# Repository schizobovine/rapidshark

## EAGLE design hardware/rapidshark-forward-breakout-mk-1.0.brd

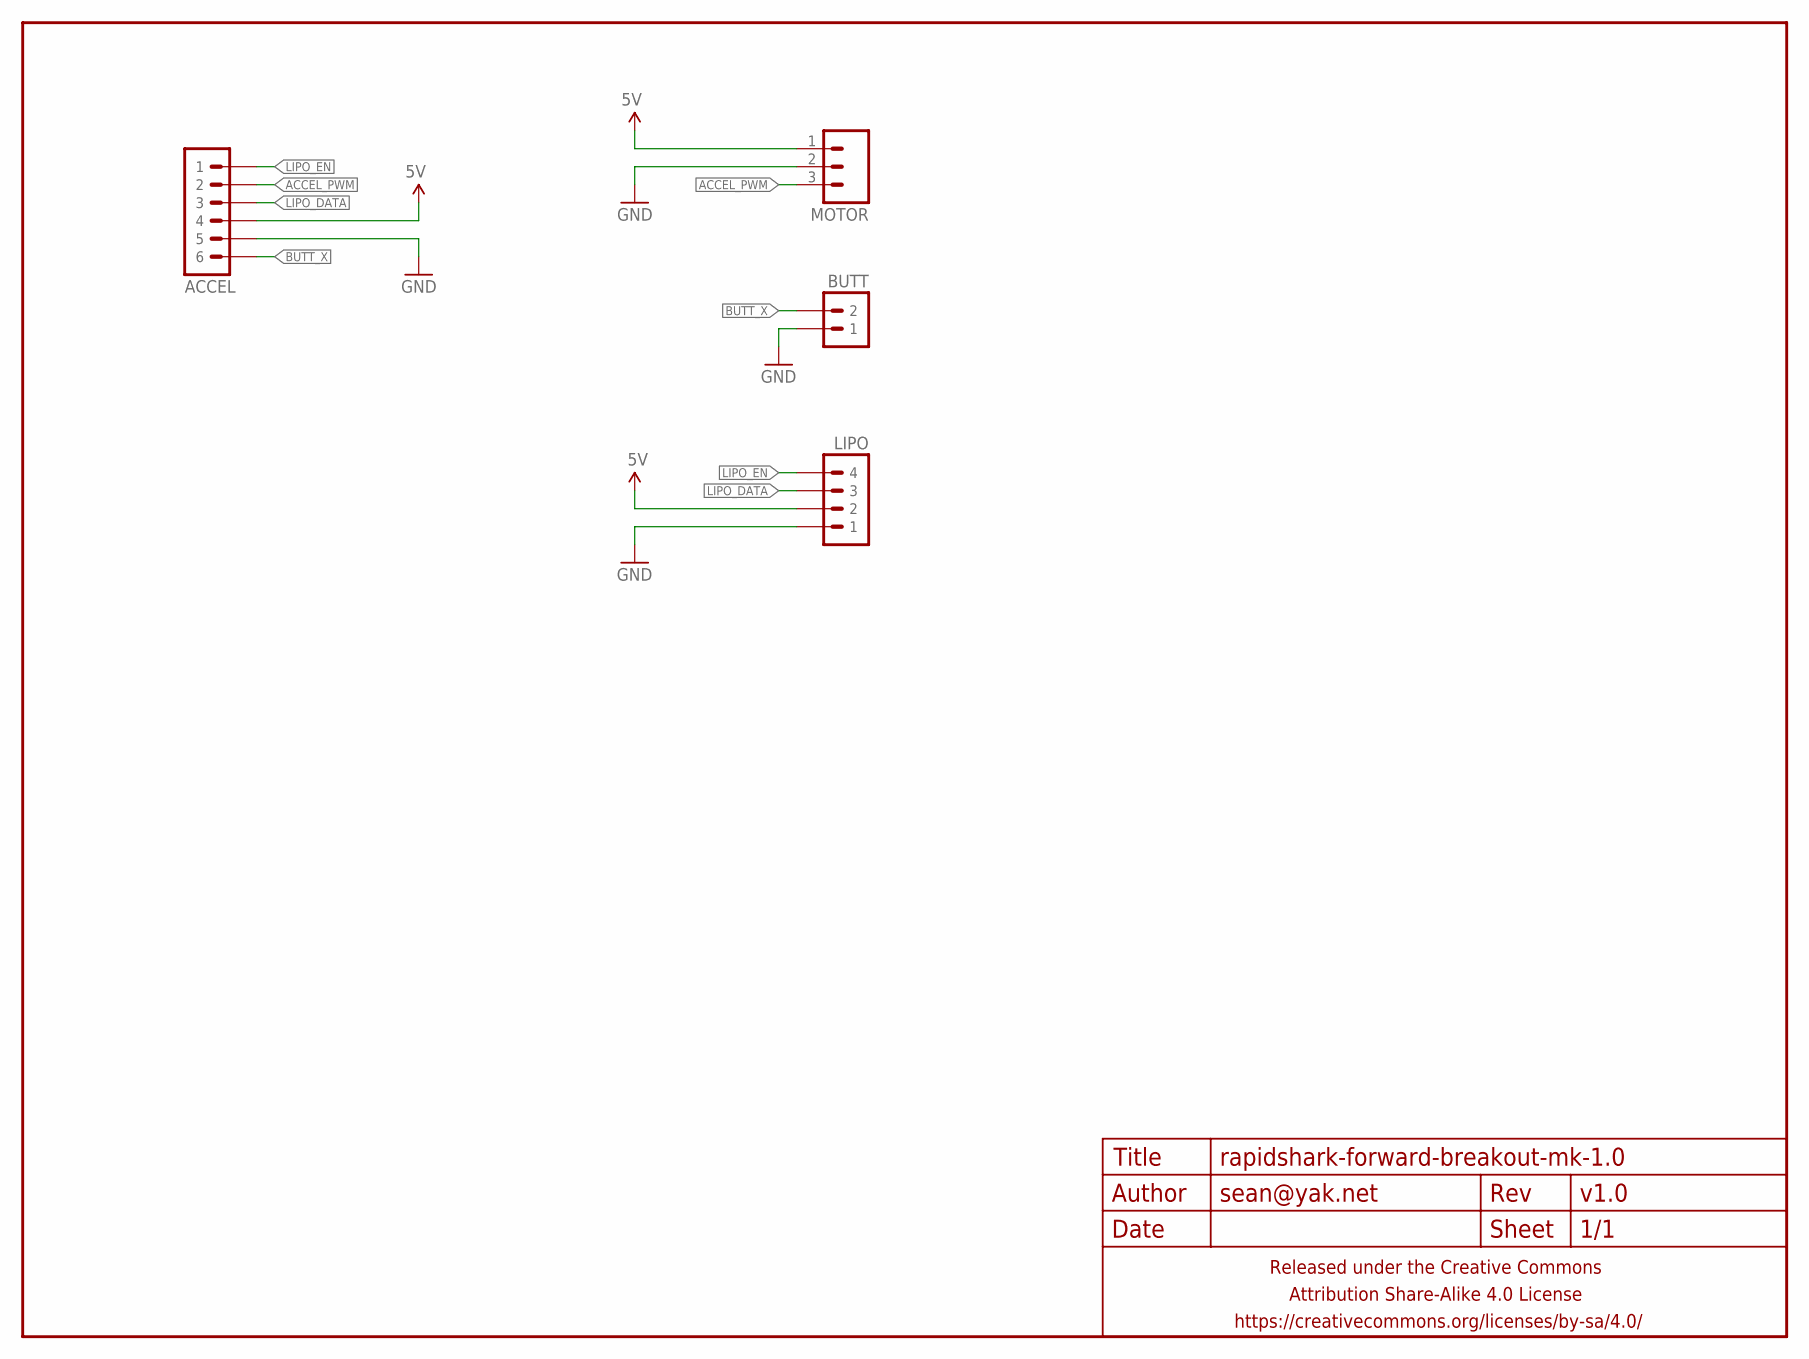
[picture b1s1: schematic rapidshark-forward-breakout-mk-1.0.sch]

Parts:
ACCEL: M06JST-PH-PTH-VERT; JST-6-PH-VERT-PTH
BUTT: M02JST-PTH-VERT; JST-2-PH-VERT-PTH
FRAME1: FRAME-LETTERNO_PACKAGE; DUMMY
LIPO: M04JST-PTH-VERT; JST-4-PH-VERT-PTH
MOTOR: M03JST-PTH-VERT; JST-3-PH-VERT-PTH

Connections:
5V: ACCEL.4, LIPO.2, MOTOR.1
ACCEL_PWM: ACCEL.2, MOTOR.3
BUTT_X: ACCEL.6, BUTT.2
GND: ACCEL.5, BUTT.1, LIPO.1, MOTOR.2
LIPO_DATA: ACCEL.3, LIPO.3
LIPO_EN: ACCEL.1, LIPO.4

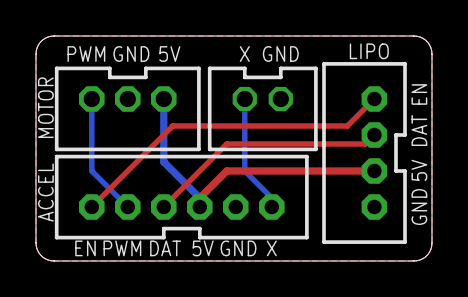
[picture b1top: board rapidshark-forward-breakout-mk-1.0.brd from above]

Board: 2 copper layers, 22.0 x 12.5 mm, 5 parts (1 on the bottom side), 6 nets.

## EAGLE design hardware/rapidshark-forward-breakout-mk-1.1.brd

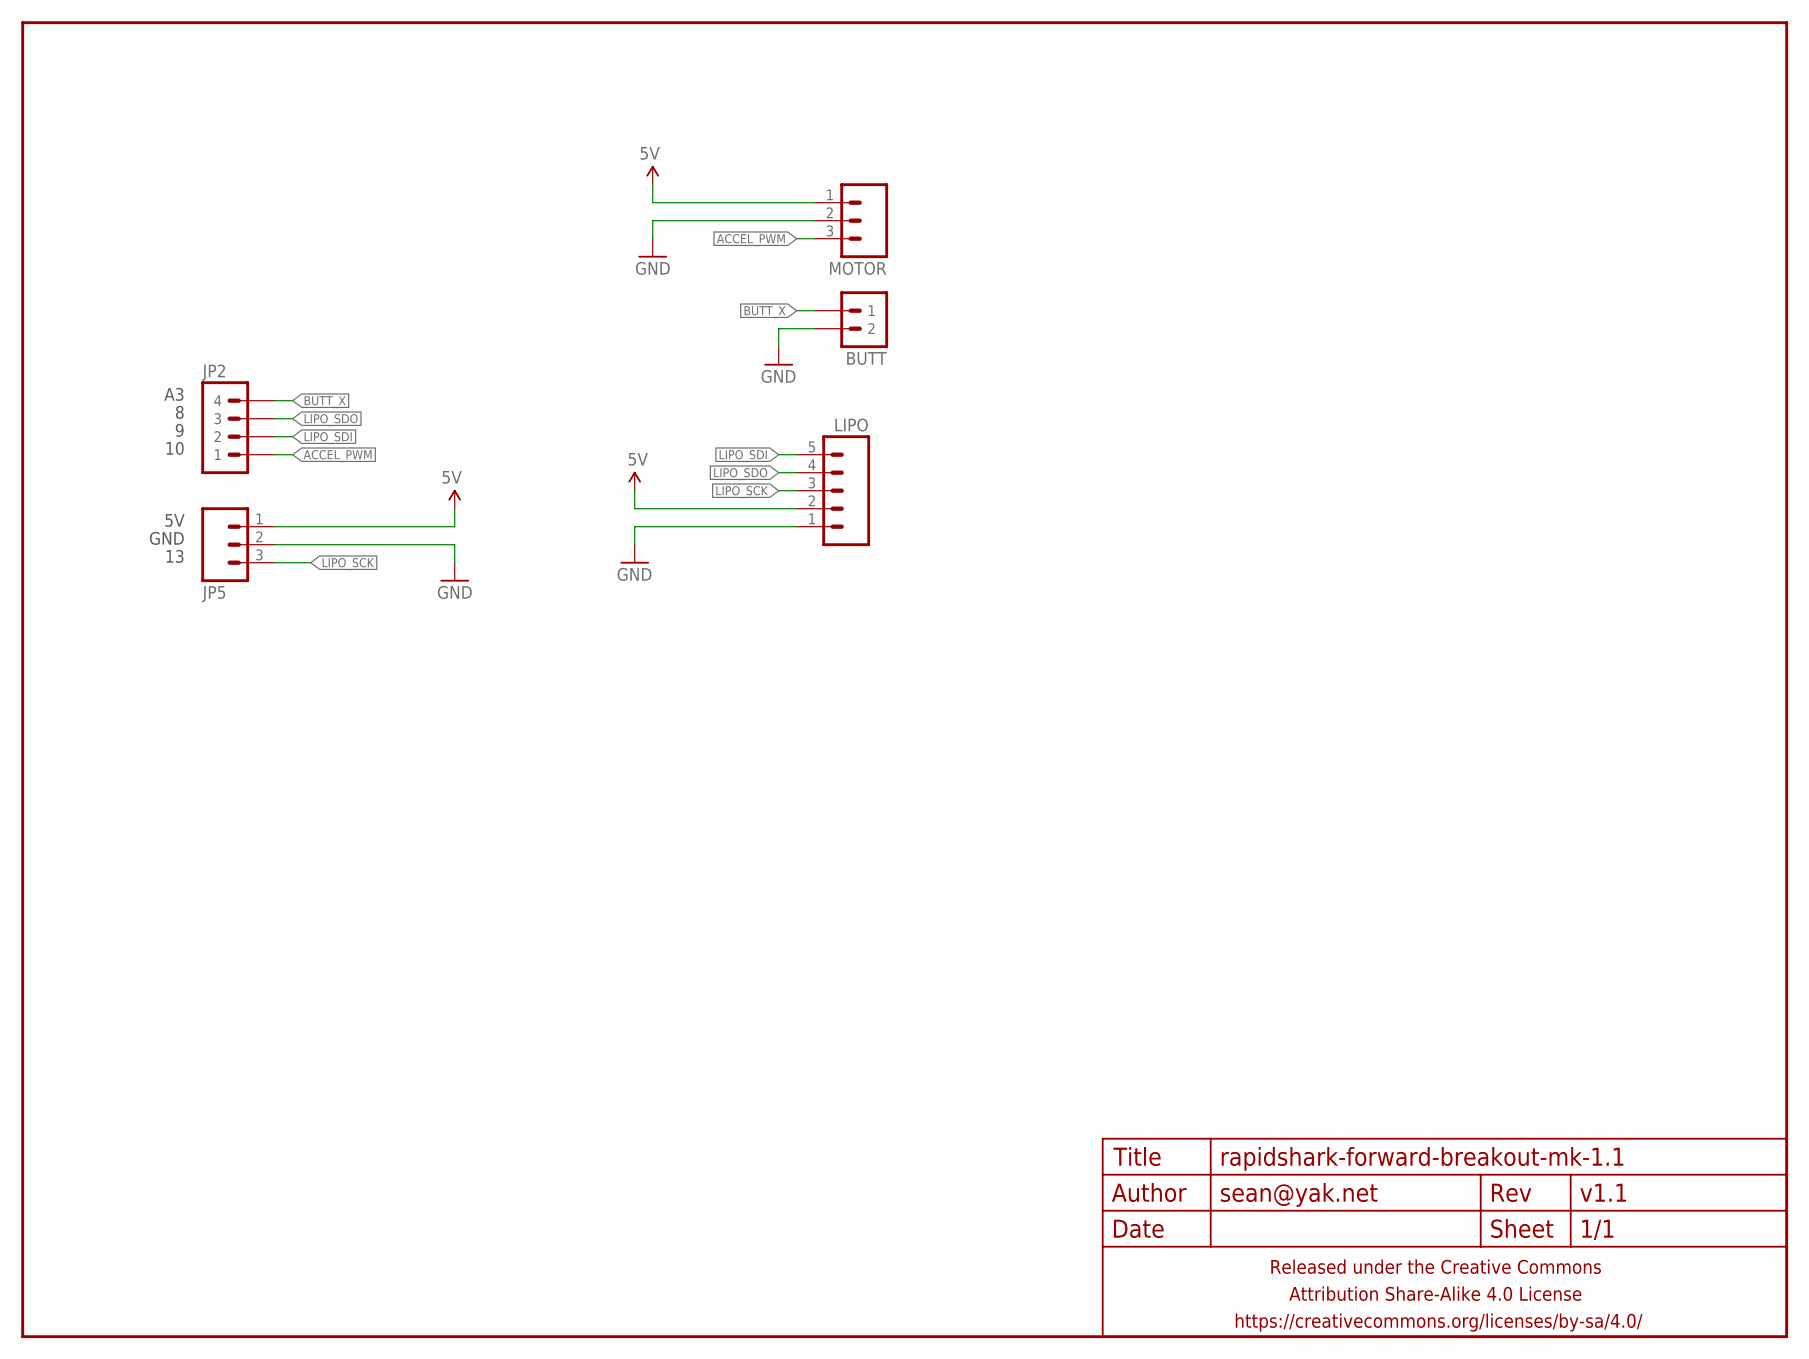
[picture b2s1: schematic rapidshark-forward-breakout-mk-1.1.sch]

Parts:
BUTT: M02JST-PTH-VERT; JST-2-PH-VERT-PTH
FRAME1: FRAME-LETTERNO_PACKAGE; DUMMY
JP2: M04JST-PTH-VERT; JST-4-PH-VERT-PTH
JP5: M03JST-PTH-VERT; JST-3-PH-VERT-PTH
LIPO: M05JST-PH-VERT-PTH; JST-5-PH-VERT-PTH
MOTOR: M03JST-PTH-VERT; JST-3-PH-VERT-PTH

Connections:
5V: JP5.1, LIPO.2, MOTOR.1
ACCEL_PWM: JP2.1, MOTOR.3
BUTT_X: BUTT.1, JP2.4
GND: BUTT.2, JP5.2, LIPO.1, MOTOR.2
LIPO_SCK: JP5.3, LIPO.3
LIPO_SDI: JP2.2, LIPO.5
LIPO_SDO: JP2.3, LIPO.4

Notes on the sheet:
GND

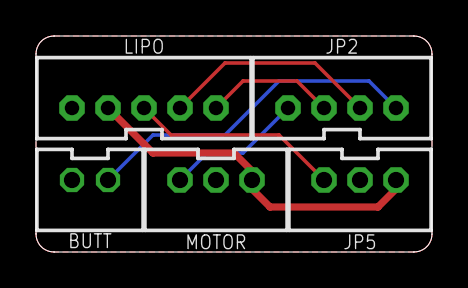
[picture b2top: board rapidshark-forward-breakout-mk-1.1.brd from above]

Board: 2 copper layers, 22.0 x 12.0 mm, 6 parts (1 on the bottom side), 7 nets.

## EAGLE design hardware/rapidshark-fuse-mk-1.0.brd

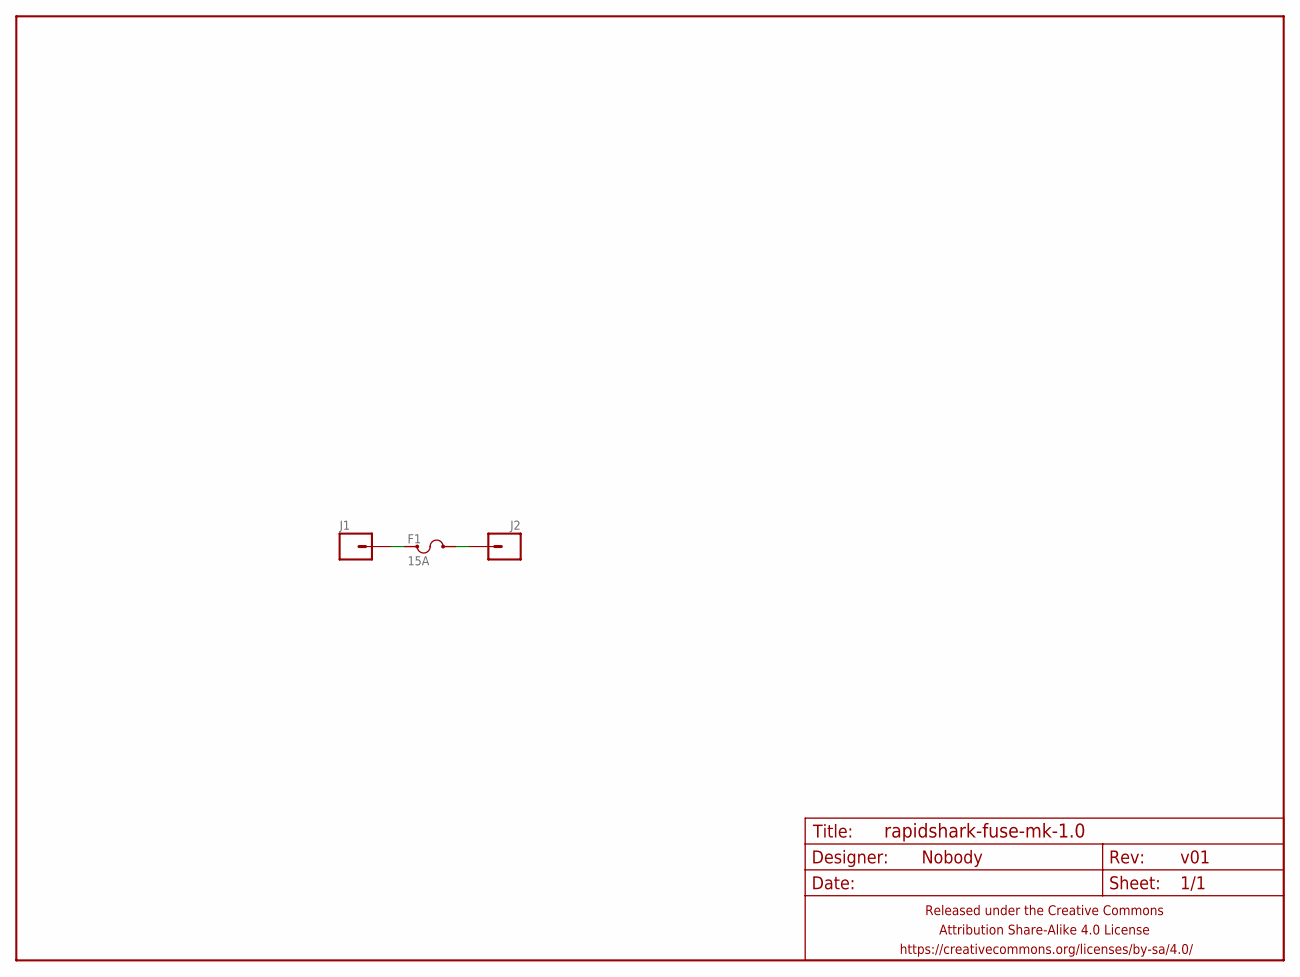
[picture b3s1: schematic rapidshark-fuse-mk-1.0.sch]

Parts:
F1: 15A; KEYSTONE-MINI-AUTO-FUSE-HOLDER
FRAME1: FRAME-LETTERNO_PACKAGE; DUMMY
J1, J2: M0112AWG-OFFSET; 1X01-12AWG-OFFSET

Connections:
A: F1.P1@1 (1), F1.P1@2 (1), J1.1
B: F1.P2@1 (2), F1.P2@2 (2), J2.1

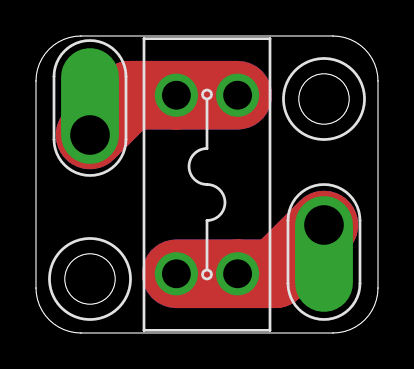
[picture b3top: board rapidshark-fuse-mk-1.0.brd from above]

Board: 2 copper layers, 19.0 x 16.5 mm, 4 parts (1 on the bottom side), 2 nets.

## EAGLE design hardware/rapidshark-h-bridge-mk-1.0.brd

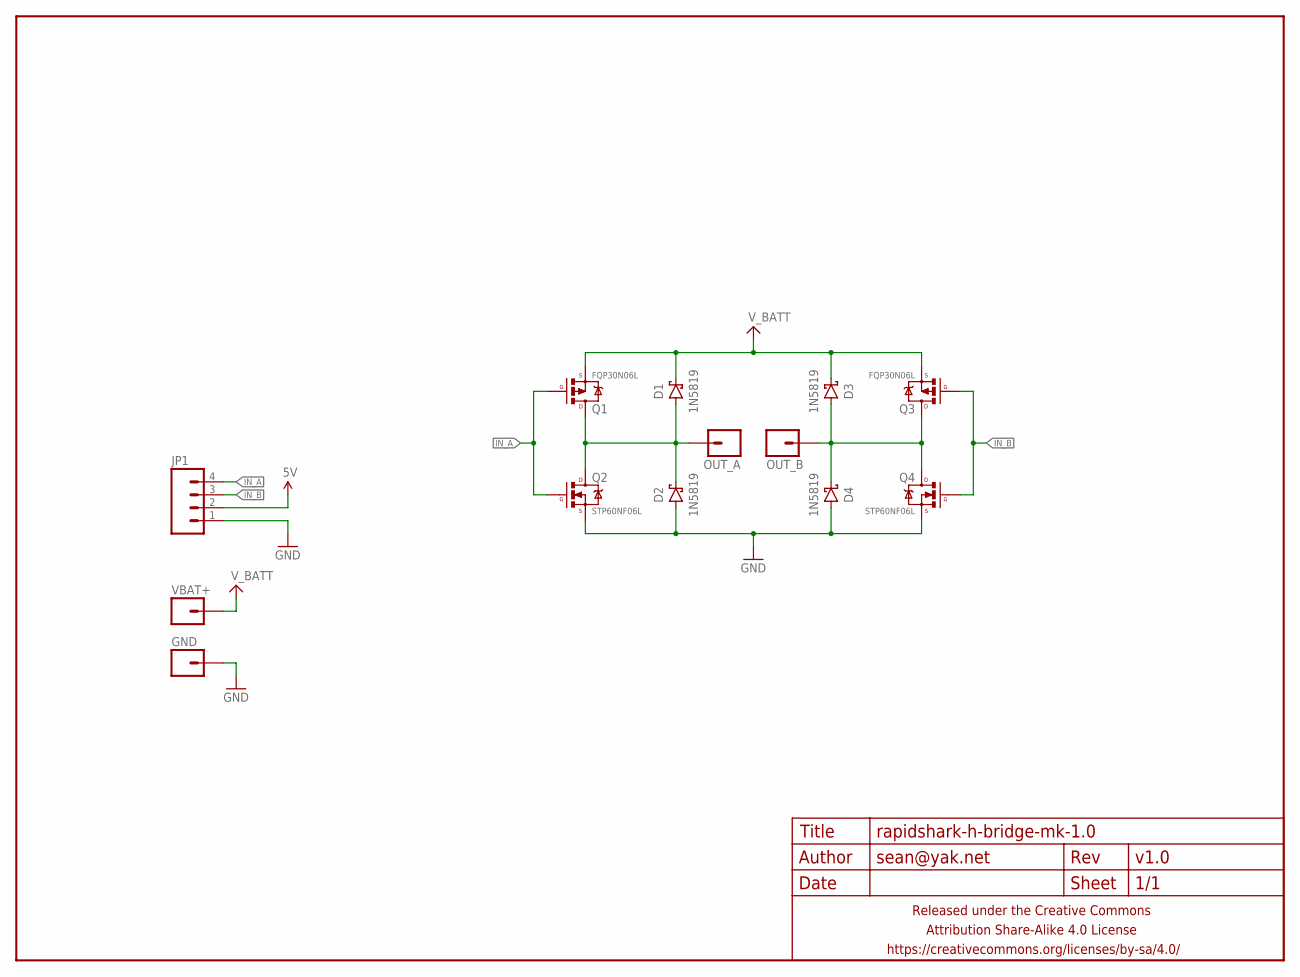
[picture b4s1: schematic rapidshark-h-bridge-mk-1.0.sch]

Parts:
D1, D2, D3, D4: 1N5819; DIODE-SCHOTTKY-10.16MM
FRAME1: FRAME-LETTERNO_PACKAGE; DUMMY
GND: M0112AWG; 1X01-12AWG
JP1: M04PTH; 1X04-PTH-VERT
OUT_A: M0112AWG; 1X01-12AWG
OUT_B: M0112AWG; 1X01-12AWG
Q1, Q3: FQP30N06L; TO220-THERMPAD
Q2, Q4: STP60NF06L; TO220-THERMPAD
VBAT+: M0112AWG; 1X01-12AWG

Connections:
5V: JP1.2
A: D1.A, D2.C, OUT_A.1, Q1.2@1 (D), Q1.2@2 (D), Q2.2@1 (D), Q2.2@2 (D)
B: D3.A, D4.C, OUT_B.1, Q3.2@1 (D), Q3.2@2 (D), Q4.2@1 (D), Q4.2@2 (D)
GND: D2.A, D4.A, GND.1, JP1.1, Q2.3 (S), Q4.3 (S)
IN_A: JP1.4, Q1.1 (G), Q2.1 (G)
IN_B: JP1.3, Q3.1 (G), Q4.1 (G)
V_BATT: D1.C, D3.C, Q1.3 (S), Q3.3 (S), VBAT+.1

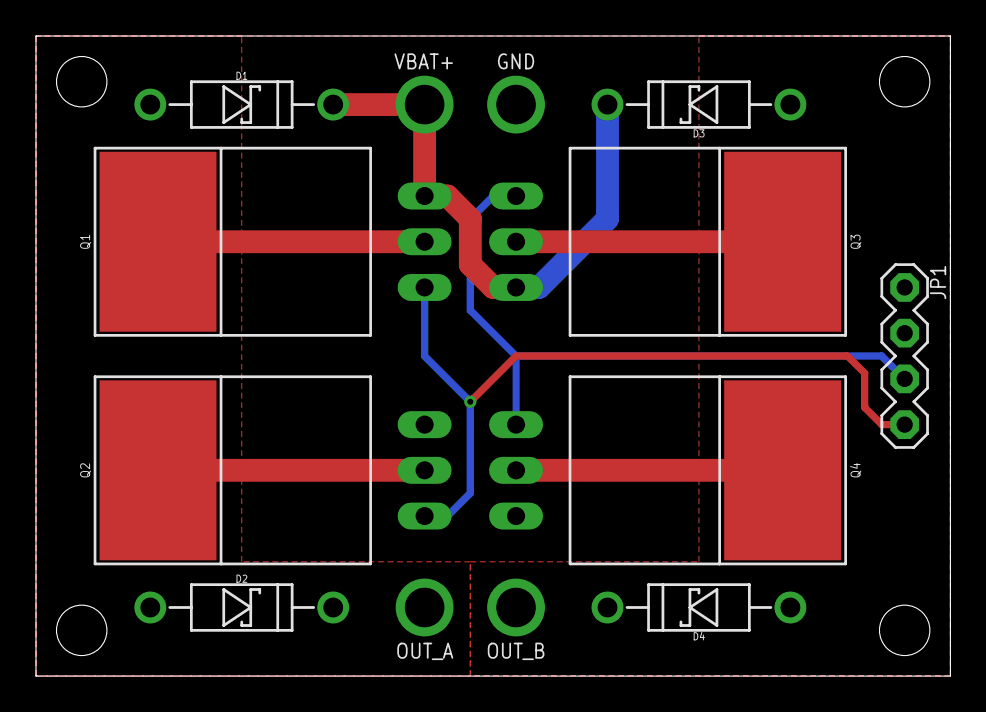
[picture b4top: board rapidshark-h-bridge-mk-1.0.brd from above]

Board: 2 copper layers, 50.8 x 35.6 mm, 14 parts (1 on the bottom side), 6 nets.

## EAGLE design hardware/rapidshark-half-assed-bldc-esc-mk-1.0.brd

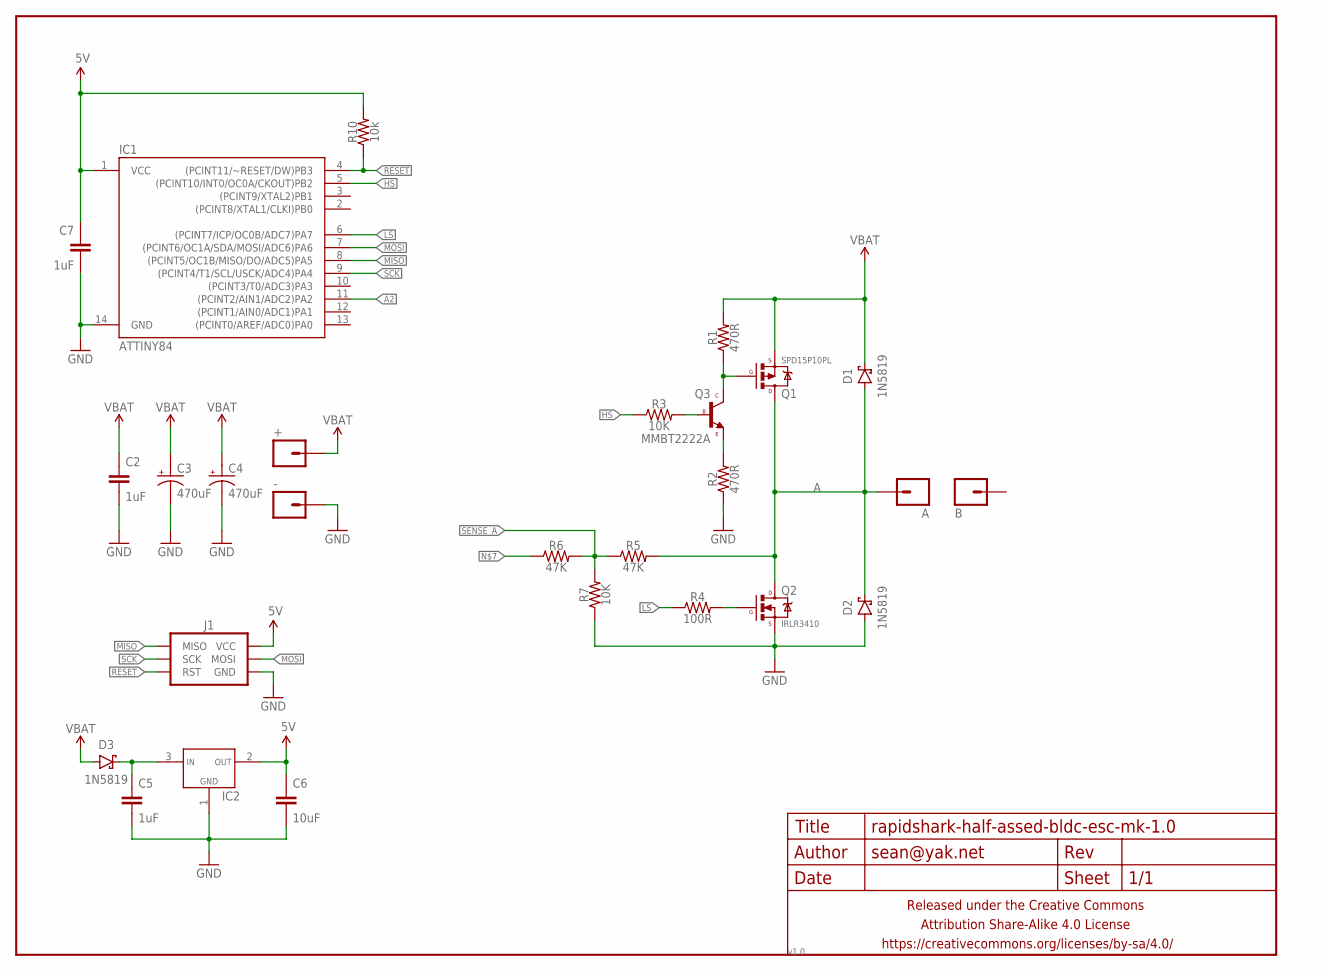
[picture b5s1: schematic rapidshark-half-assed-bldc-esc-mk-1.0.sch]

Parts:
+: M01PTH-1.4MM; 1X01-1.4MM-CIR
-: M01PTH-1.4MM; 1X01-1.4MM-CIR
A: M01PTH-1.4MM; 1X01-1.4MM-CIR
B: M01PTH-1.4MM; 1X01-1.4MM-CIR
C2, C7: 1uF; C0603-TIGHTER
C3, C4: 470uF; E5-10,5
C5: 1uF; C0805-TIGHTER
C6: 10uF; C0805-TIGHTER
D1, D2: 1N5819; SMA-DIODE-SCHOTTKY
D3: 1N5819; SOD323-SCHOTTKY
FRAME1: FRAME-LETTERNO_PACKAGE; DUMMY
IC1: ATTINY84; SO14
IC2: VREG_1117SOT-23; SOT23
J1: AVR_SPI_PRG_6INLINE; AVR_MINI_PROG
Q1: SPD15P10PL; DPAK
Q2: IRLR3410; DPAK
Q3: MMBT2222A; SOT23
R1, R2: 470R; R0603-TIGHTER
R3, R7: 10K; R0603-TIGHTER
R4: 100R; R0603-TIGHTER
R5, R6: 47K; R0603-TIGHTER
R10: 10k; R0603-TIGHTER

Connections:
5V: C6.1, C7.1, IC1.1 (VCC), IC2.2 (VOUT), J1.2 (VCC), R10.2
A: A.P$1, D1.A, D2.C, Q1.4 (D), Q2.4 (D), R5.2
A2: IC1.11 ((PCINT2/AIN1/ADC2)PA2)
GND: -.P$1, C2.2, C3.-, C4.-, C5.2, C6.2, C7.2, D2.A, IC1.14 (GND), IC2.1 (GND), J1.6 (GND), Q2.3 (S), R2.1, R7.1
HS: IC1.5 ((PCINT10/INT0/OC0A/CKOUT)PB2), R3.1
LS: IC1.6 ((PCINT7/ICP/OC0B/ADC7)PA7), R4.1
MISO: IC1.8 ((PCINT5/OC1B/MISO/DO/ADC5)PA5), J1.1 (MISO)
MOSI: IC1.7 ((PCINT6/OC1A/SDA/MOSI/ADC6)PA6), J1.4 (MOSI)
unnamed: Q1.1 (G), Q3.3 (C), R1.1
unnamed: Q3.2 (E), R2.2
unnamed: Q3.1 (B), R3.2
unnamed: Q2.1 (G), R4.2
unnamed: C5.1, D3.C, IC2.3 (VIN)
RESET: IC1.4 ((PCINT11/~RESET/DW)PB3), J1.5 (RST), R10.1
SCK: IC1.9 ((PCINT4/T1/SCL/USCK/ADC4)PA4), J1.3 (SCK)
SENSE_A: R5.1, R6.2, R7.2
VBAT: +.P$1, C2.1, C3.+, C4.+, D1.C, D3.A, Q1.3 (S), R1.2

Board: 2 copper layers, 31 parts (4 on the bottom side), 16 nets, no tracks yet.

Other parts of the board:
U$1: COW_SMALL_METAL_NOTEXT
U$2: CC-BY-SA-4.0-NO-URL
U$3: OSHWLOGO_TINY_SILKONLY

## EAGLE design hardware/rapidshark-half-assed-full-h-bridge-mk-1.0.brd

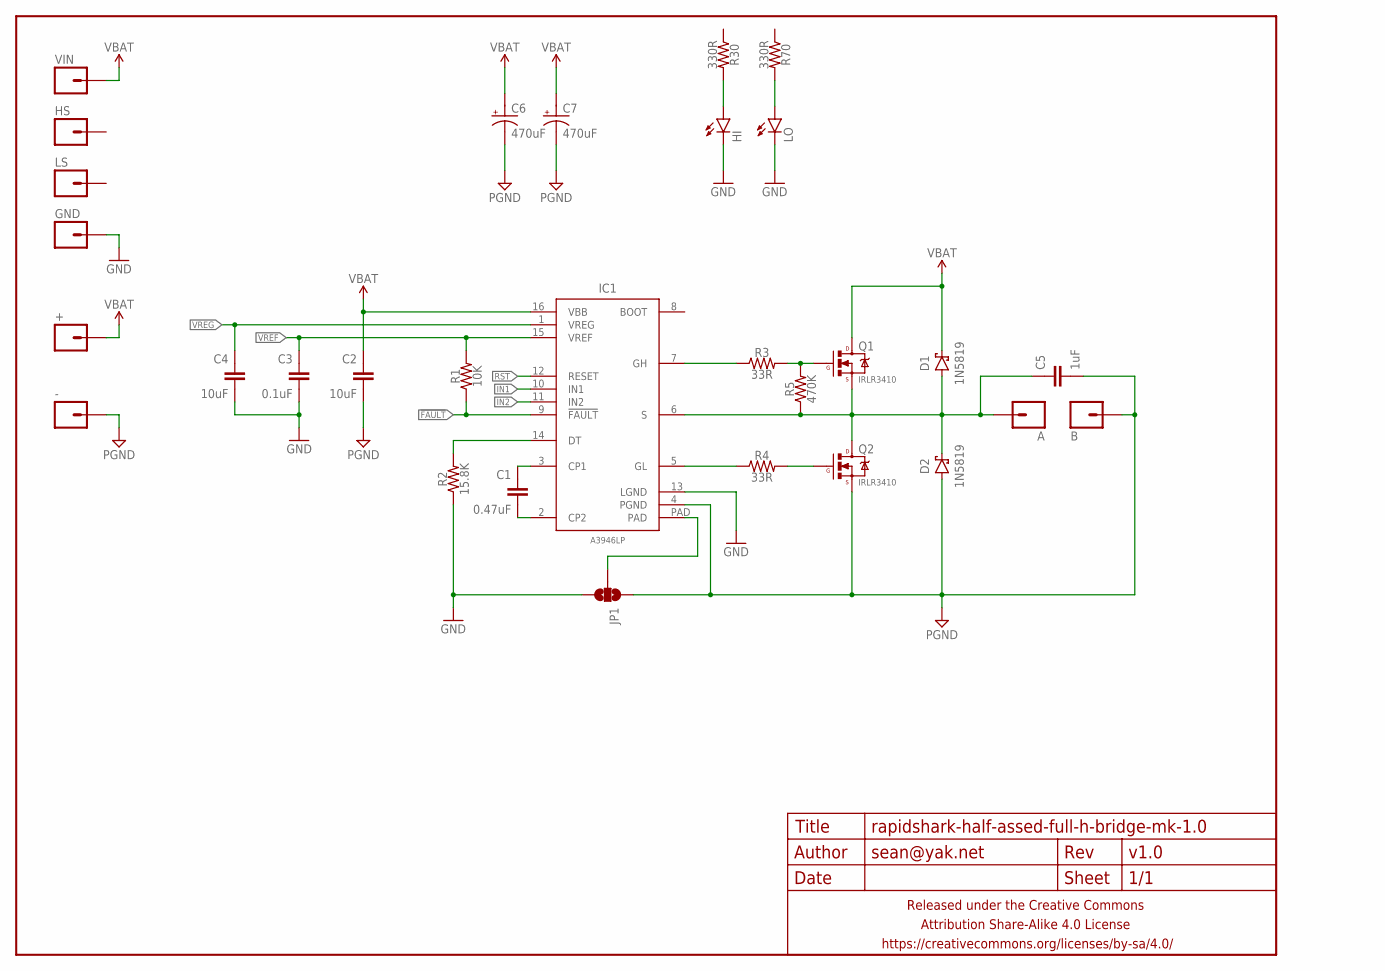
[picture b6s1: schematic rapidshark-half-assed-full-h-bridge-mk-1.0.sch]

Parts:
+: M01PTH-1.9MM; 1X01-1.9MM-CIR
-: M01PTH-1.9MM; 1X01-1.9MM-CIR
A: M01PTH-1.9MM; 1X01-1.9MM-CIR
B: M01PTH-1.9MM; 1X01-1.9MM-CIR
C1: 0.47uF; C0603-TIGHTER
C2, C4: 10uF; C0805-TIGHTER
C3: 0.1uF; C0603-TIGHTER
C5: 1uF; C0603-TIGHTER
C6, C7: 470uF; E5-10,5
D1, D2: 1N5819; SMA-DIODE-SCHOTTKY
FRAME1: FRAME-LETTERNO_PACKAGE; DUMMY
GND: M01PTH; 1X01
HI: LED0603-TIGHT; LED-0603-TIGHT
HS: M01PTH; 1X01
IC1: A3946LP; TSSOP-16-PAD
JP1: JUMPER-PAD-3-NOFULL_BOX_SILK; PAD-JUMPER-3-NO_YES_SILK_FULL_BOX
LO: LED0603-TIGHT; LED-0603-TIGHT
LS: M01PTH; 1X01
Q1, Q2: IRLR3410; DPAK
R1: 10K; R0603-TIGHTER
R2: 15.8K; R0603-TIGHTER
R3, R4: 33R; R0603-TIGHTER
R5: 470K; R0603-TIGHTER
R30, R70: 330R; R0603-TIGHTER
VIN: M01PTH; 1X01

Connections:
!FAULT: IC1.9 (!FAULT), R1.1
A: A.P$1, C5.1, D1.A, D2.C, IC1.6 (S), Q1.3 (S), Q2.4 (D), R5.1
GND: C3.2, C4.2, GND.1, HI.C, IC1.13 (LGND), JP1.3, LO.C, R2.1
IN1: IC1.10 (IN1)
IN2: IC1.11 (IN2)
unnamed: Q2.1 (G), R4.2
unnamed: C1.1, IC1.3 (CP1)
unnamed: LO.A, R70.2
unnamed: HI.A, R30.2
unnamed: Q1.1 (G), R3.2, R5.2
unnamed: C1.2, IC1.2 (CP2)
unnamed: IC1.14 (DT), R2.2
unnamed: IC1.PAD, JP1.2
unnamed: IC1.5 (GL), R4.1
unnamed: IC1.7 (GH), R3.1
PGND: -.P$1, B.P$1, C2.2, C5.2, C6.-, C7.-, D2.A, IC1.4 (PGND), JP1.1, Q2.3 (S)
RST: IC1.12 (RESET)
VBAT: +.P$1, C2.1, C6.+, C7.+, D1.C, IC1.16 (VBB), Q1.4 (D), VIN.1
VREF: C3.1, IC1.15 (VREF), R1.2
VREG: C4.1, IC1.1 (VREG)

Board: 2 copper layers, 34 parts (5 on the bottom side), 17 nets, no tracks yet.

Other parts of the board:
U$1: COW
U$2: CC-BY-SA-4.0-NO-URL
U$3: OSHWLOGO_5MM

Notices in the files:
parts and their libraries:
a_parts: Released under the Creative Commons Attribution Share-Alike 4.0 License
a_parts: https://creativecommons.org/licenses/by-sa/4.0
a_parts: Released under the Creative Commons
